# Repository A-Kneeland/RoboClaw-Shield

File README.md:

# RoboClaw-Shield
A shield that gives better connections for RoboClaw Motor Controllers

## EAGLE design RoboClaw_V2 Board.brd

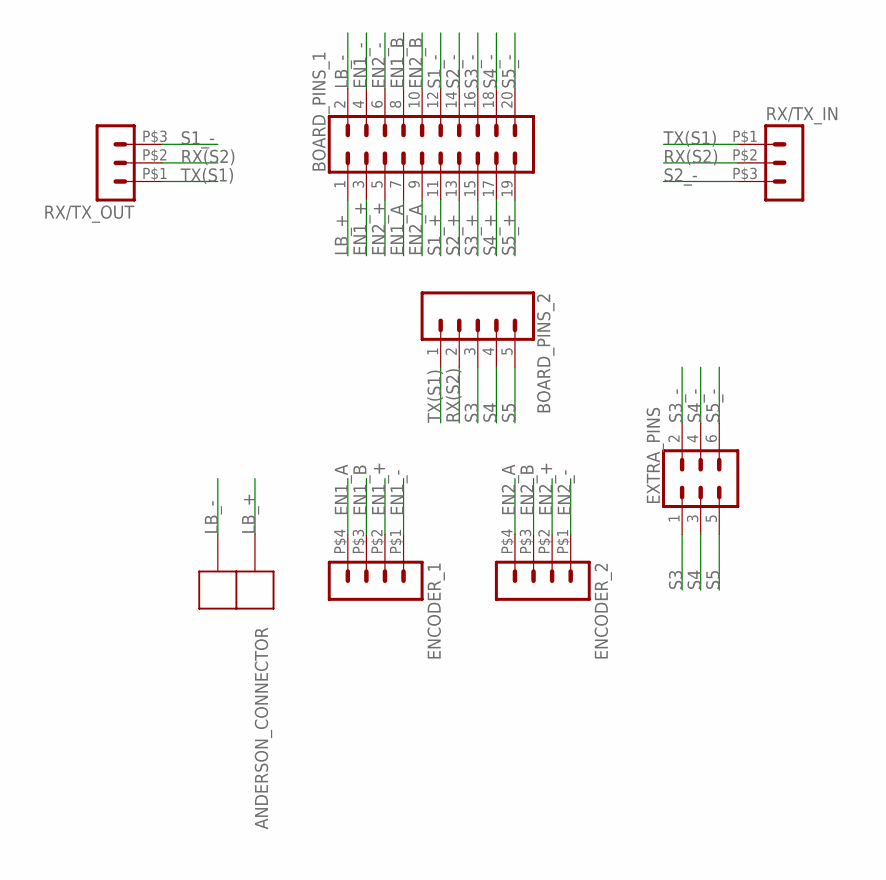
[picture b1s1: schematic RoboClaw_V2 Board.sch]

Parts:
ANDERSON_CONNECTOR: 2PIN-HEADERANDERSON_RIGHTANGLE; ANDERSON_RIGHTANGLE_X2
BOARD_PINS_1: CONN_10X2NOSILK; 2X10_NOSILK
BOARD_PINS_2: CONN_05NO_SILK; 1X05_NO_SILK
ENCODER_1, ENCODER_2: HEADER_POS4_43045-0401; 43045-0400
EXTRA_PINS: CONN_03X2NO_SILK; 2X3-NS
RX/TX_IN: HEADER_POS3_43650-0300; 43650-0300
RX/TX_OUT: HEADER_POS3_43650-0300; 43650-0300

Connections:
EN1_+: BOARD_PINS_1.3, ENCODER_1.P$2 (2)
EN1_-: BOARD_PINS_1.4, ENCODER_1.P$1 (1)
EN1_A: BOARD_PINS_1.7, ENCODER_1.P$4 (4)
EN1_B: BOARD_PINS_1.8, ENCODER_1.P$3 (3)
EN2_+: BOARD_PINS_1.5, ENCODER_2.P$2 (2)
EN2_-: BOARD_PINS_1.6, ENCODER_2.P$1 (1)
EN2_A: BOARD_PINS_1.9, ENCODER_2.P$4 (4)
EN2_B: BOARD_PINS_1.10, ENCODER_2.P$3 (3)
LB_+: ANDERSON_CONNECTOR.P1, BOARD_PINS_1.1
LB_-: ANDERSON_CONNECTOR.P2, BOARD_PINS_1.2
RX(S2): BOARD_PINS_2.2, RX/TX_IN.P$2 (2), RX/TX_OUT.P$2 (2)
S1_+: BOARD_PINS_1.11
S1_-: BOARD_PINS_1.12, RX/TX_OUT.P$3 (3)
S2_+: BOARD_PINS_1.13
S2_-: BOARD_PINS_1.14, RX/TX_IN.P$3 (3)
S3: BOARD_PINS_2.3, EXTRA_PINS.1
S3_+: BOARD_PINS_1.15
S3_-: BOARD_PINS_1.16, EXTRA_PINS.2
S4: BOARD_PINS_2.4, EXTRA_PINS.3
S4_+: BOARD_PINS_1.17
S4_-: BOARD_PINS_1.18, EXTRA_PINS.4
S5: BOARD_PINS_2.5, EXTRA_PINS.5
S5_+: BOARD_PINS_1.19
S5_-: BOARD_PINS_1.20, EXTRA_PINS.6
TX(S1): BOARD_PINS_2.1, RX/TX_IN.P$1 (1), RX/TX_OUT.P$1 (1)

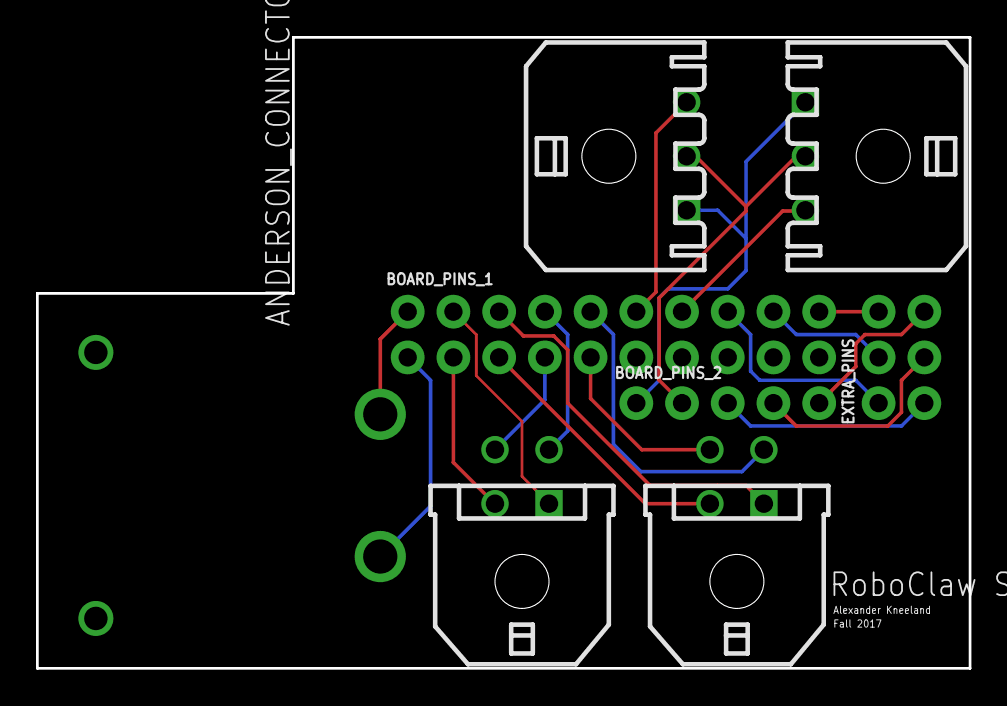
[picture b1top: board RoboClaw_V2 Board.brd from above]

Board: 2 copper layers, 51.8 x 35.1 mm, 8 parts (0 on the bottom side), 20 nets.

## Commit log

2018-01-30 added github cheat sheet
2018-01-30 i Tried to make stuff work. hopefully succeeded
2018-01-30 more tests# Please enter the commit message for your changes. Lines starting
2018-01-31 Added in some new connectors in the schematic and resized board
2018-01-31 connected nets to encoders/serial lines/battery
2018-02-01 Wired the schematic. Placed and wired the board. First Draft
2018-02-02 beefed up connecting wires and moved molex connector to not hit the capacitor on the roboclaw

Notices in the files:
parts and their libraries:
SparkFun-Connectors: Licensing: Creative Commons ShareAlike 4.0 International - https://creativecommons.org/licenses/by-sa/4.0
